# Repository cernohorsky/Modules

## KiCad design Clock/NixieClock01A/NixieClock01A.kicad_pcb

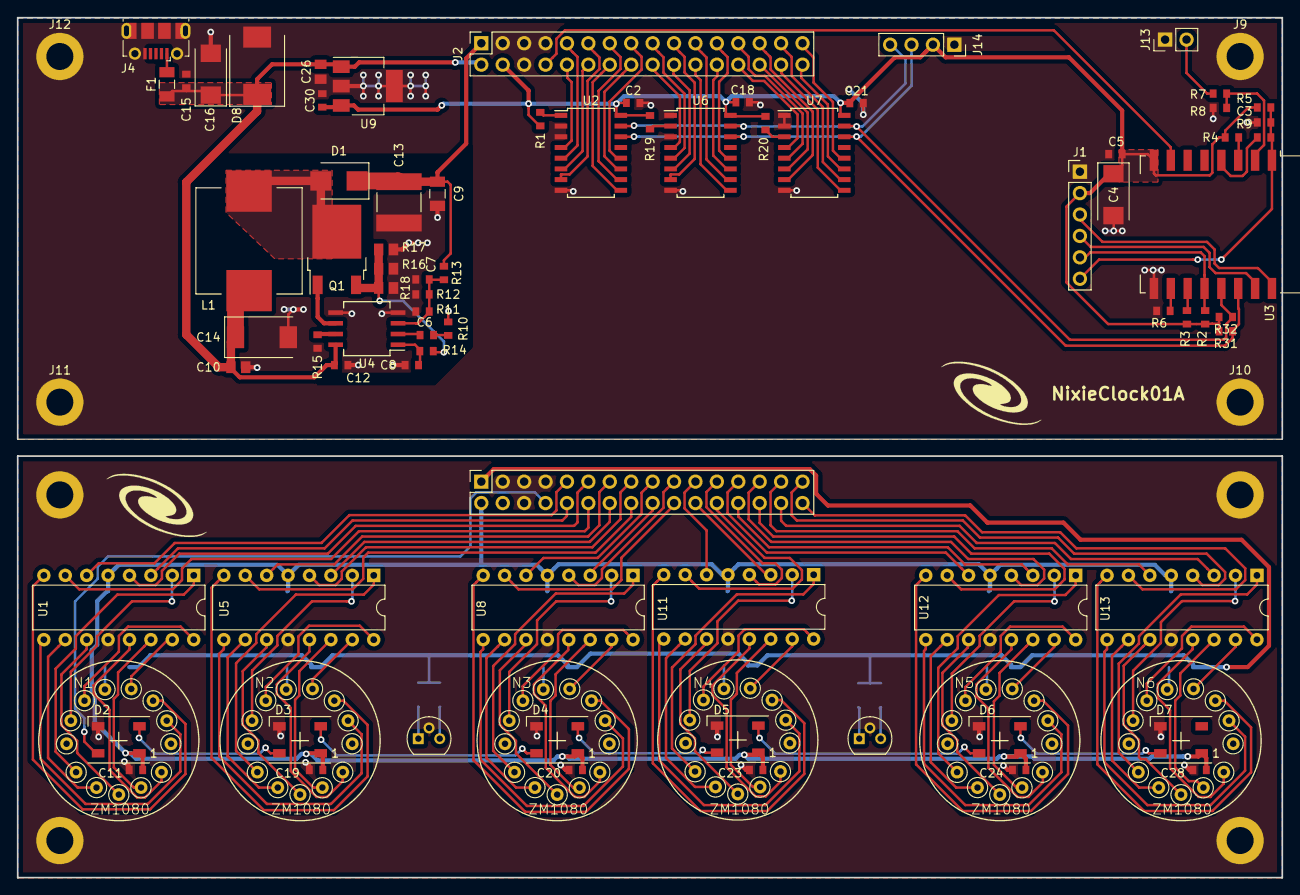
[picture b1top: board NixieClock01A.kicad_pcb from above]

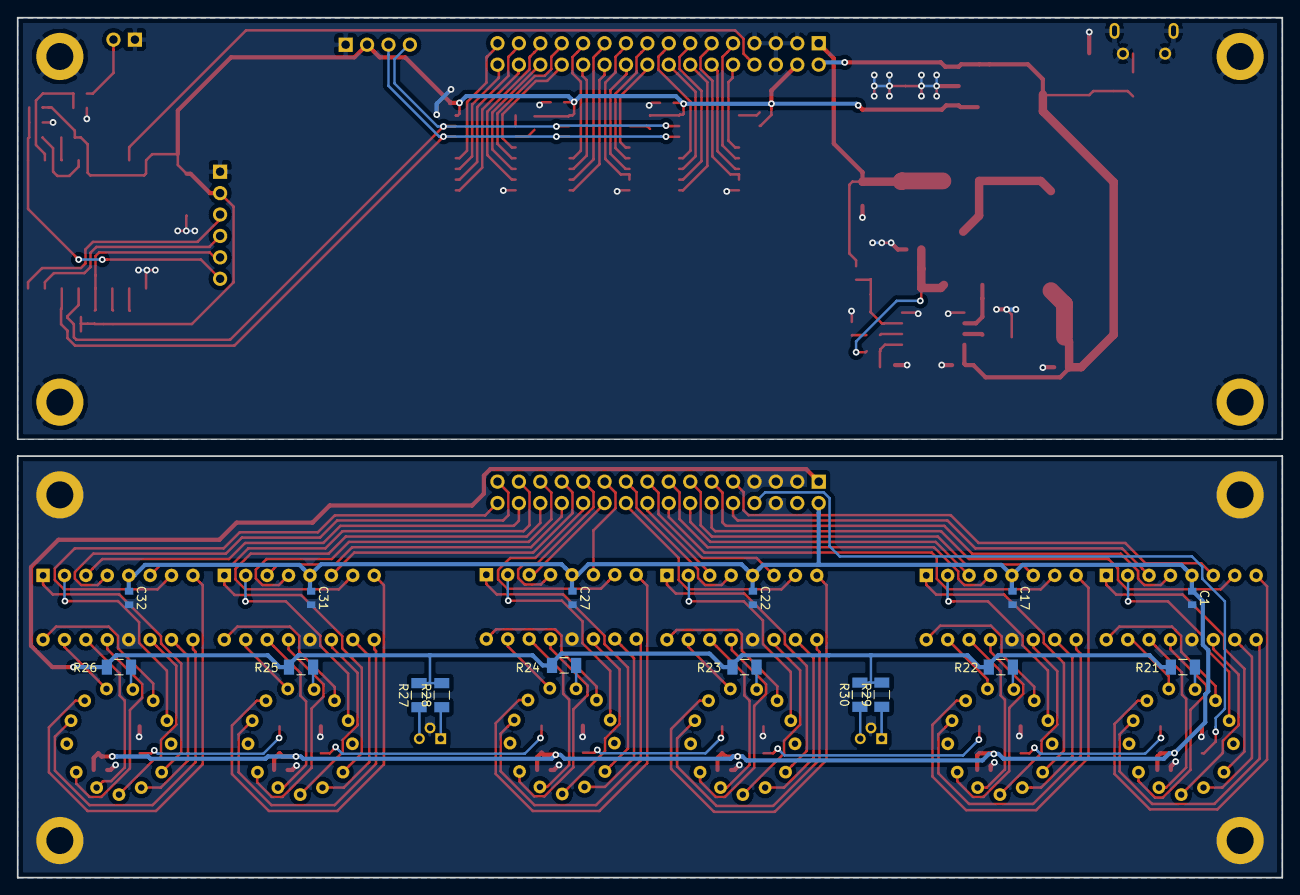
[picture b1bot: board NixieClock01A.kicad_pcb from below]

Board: 2 copper layers, 150.0 x 102.0 mm, 107 parts (16 on the bottom side), 128 nets.

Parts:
C1, C2, C3, C5, C11, C12, C15, C17, C18, C19, C20, C21, C22, C23, C24, C27, C28, C31, C32: 100n; C_0603_1608Metric
C4, C16: TPSC107K010R0075; CP_EIA-6032-28_Kemet-C
C6, C7: 22n; C_0603_1608Metric
C8: C; C_0603_1608Metric
C9: 100n/200V; C_1206_3216Metric
C10, C26: 10u; C_0805_2012Metric
C13: 1u/200V; C_2220_5650Metric
C14: 100u; CP_EIA-7343-31_Kemet-D
C30: 1u; C_0603_1608Metric
D1: D_Schottky; D_SMB
D2, D3, D4, D5, D6, D7: WS2812B; LED_WS2812B_PLCC4_5.0x5.0mm_P3.2mm
D8: D_TVS; D_SMC
F1: Fuse; Fuse_1206_3216Metric
J1: Conn_01x06_Male; PinHeader_1x06_P2.54mm_Vertical
J2, J3: Conn_02x16_Odd_Even; PinSocket_2x16_P2.54mm_Vertical
J4: USB_B_Micro; USB_Micro-B_Molex-105017-0001
J5, J6, J7, J8, J9, J10, J11, J12: Conn_01x01_Male; MountingHole_3.2mm_M3_DIN965_Pad
J13: Conn_01x02_Male; PinHeader_1x02_P2.54mm_Vertical
J14: Conn_01x04_Male; PinSocket_1x04_P2.54mm_Vertical
L1: L_Core_Ferrite; L_Wuerth_WE-PD-Typ-LS_Handsoldering
LA1, LA2: Lamp_Neon; TO-92
N1, N2, N3, N4, N5, N6: ZM1080
Q1: Q_NMOS_GDS; TO-252-2
R1, R11, R12, R13, R14, R19, R20: R; R_0603_1608Metric
R2, R3, R4, R5, R6: 12k; R_0603_1608Metric
R7: 330k; R_0603_1608Metric
R8: 100k; R_0603_1608Metric
R9: 470R; R_0603_1608Metric
R10: 4k7; R_0603_1608Metric
R15: 40k; R_0603_1608Metric
R16, R17, R18: R; R_0805_2012Metric
R21, R22, R23, R24, R25, R26: 27k; R_1206_3216Metric
R27, R28, R29, R30: 1M; R_1206_3216Metric
R31, R32: 4K7; R_0603_1608Metric
U1, U5, U8, U11, U12, U13: 74141; DIP-16_W7.62mm
U2, U6, U7: PCF8574; SOIC-16W_5.3x10.2mm_P1.27mm
U3: ESP-12E
U4: LM3478; SO-8_5.3x6.2mm_P1.27mm
U9: TC1262-33; SOT-223

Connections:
+3V3: C2.1, C4.1, C5.1, C18.1, C21.1, C30.1, J1.2, J2.4, J3.4, J14.2, R1.1, R2.2, R3.2, R4.2, R5.2, R19.1, R20.1, R31.2, R32.2, U2.16, U3.8, U6.16, U7.16, U9.3
+5V: C1.1, C10.1, C11.1, C12.1, C14.1, C15.1, C16.1, C17.1, C19.1, C20.1, C22.1, C23.1, C24.1, C26.1, C27.1, C28.1, C31.1, C32.1, D2.1, D3.1, D4.1, D5.1, D6.1, D7.1, D8.1, F1.1, J2.2, J3.2, L1.1, U1.5, U4.8, U5.5, U8.5, U9.1, U11.5, U12.5, U13.5
/A1: J2.10, J3.10, U1.3, U2.4
/A2: J2.9, J3.9, U1.6, U2.5
/A3: J2.12, J3.12, U1.7, U2.6
/A4: J2.11, J3.11, U1.4, U2.7
/ADC: R7.2, R8.1, U3.2
/ADC-IN: J13.2, R7.1
/B1: J2.14, J3.14, U2.9, U5.3
/B2: J2.13, J3.13, U2.10, U5.6
/B3: J2.16, J3.16, U2.11, U5.7
/B4: J2.15, J3.15, U2.12, U5.4
/C1: J2.18, J3.18, U6.4, U8.3
/C2: J2.17, J3.17, U6.5, U8.6
/C3: J2.20, J3.20, U6.6, U8.7
/C4: J2.19, J3.19, U6.7, U8.4
/D1: J2.22, J3.22, U6.9, U11.3
/D2: J2.21, J3.21, U6.10, U11.6
/D3: J2.24, J3.24, U6.11, U11.7
/D4: J2.23, J3.23, U6.12, U11.4
/E1: J2.26, J3.26, U7.4, U12.3
/E2: J2.25, J3.25, U7.5, U12.6
/E3: J2.28, J3.28, U7.6, U12.7
/E4: J2.27, J3.27, U7.7, U12.4
/EN: R4.1, U3.3
/F1: J2.30, J3.30, U7.9, U13.3
/F2: J2.29, J3.29, U7.10, U13.6
/F3: J2.32, J3.32, U7.11, U13.7
/F4: J2.31, J3.31, U7.12, U13.4
/GPIO0: J1.5, R2.1, U3.18
/GPIO2: R3.1, U3.17
/GPIO15: R6.1, U3.16
/NeoPix: D2.4, J2.8, J3.8, U3.7
/RST: C3.1, J1.6, R5.1, R9.1, U3.1
/RX: J1.4, U3.21
/SCL: J14.3, R31.1, U2.14, U3.20, U6.14, U7.14
/SDA: J14.4, R32.1, U2.15, U3.19, U6.15, U7.15
/TX: J1.3, U3.22
/Uanode: C9.1, C13.1, D1.1, J2.1, J3.1, R13.1, R21.1, R22.1, R23.1, R24.1, R25.1, R26.1, R27.2, R28.2, R29.2, R30.2
GND: C1.2, C2.2, C3.2, C4.2, C5.2, C7.1, C8.1, C9.2, C10.2, C11.2, C12.2, C13.2, C14.2, C15.2, C16.2, C17.2, C18.2, C19.2, C20.2, C21.2, C22.2, C23.2, C24.2, C26.2, C27.2, C28.2, C30.2, C31.2, C32.2, D2.3, D3.3, D4.3, D5.3, D6.3, D7.3, D8.2, J1.1, J2.3, J2.5, J2.6, J2.7, J3.3, J3.5, J3.6, J3.7, J4.5, J4.6, J5.1, J6.1, J7.1, J8.1, J9.1, J10.1, J11.1, J12.1, J13.1, J14.1, LA1.2, LA2.2, R6.2, R8.2, R10.1, R11.1, R12.1, R15.2, R16.2, R17.2, R18.2, U1.12, U2.2, U2.3, U2.8, U3.15, U4.4, U4.5, U5.12, U6.1, U6.3, U6.8, U7.1, U7.2, U7.8, U8.12, U9.2, U9.4, U11.12, U12.12, U13.12
unnamed: C6.1, U4.2
unnamed: C6.2, R10.2
unnamed: C7.2, R11.2, R12.2, R13.2, U4.3
unnamed: C8.2, R14.2, U4.1
unnamed: D1.2, L1.2, Q1.2
unnamed: D2.2, D3.4
unnamed: D3.2, D4.4
unnamed: D4.2, D5.4
unnamed: D5.2, D6.4
unnamed: D6.2, D7.4
unnamed: F1.2, J4.1
unnamed: LA1.1, R28.1
unnamed: LA1.3, R27.1
unnamed: LA2.1, R29.1
unnamed: LA2.3, R30.1
unnamed: N1.1, U1.15
unnamed: N1.2, U1.8
unnamed: N1.3, U1.9
unnamed: N1.5, U1.13
unnamed: N1.6, U1.14
unnamed: N1.7, U1.11
unnamed: N1.8, U1.10
unnamed: N1.9, U1.1
unnamed: N1.11, U1.2
unnamed: N1.12, U1.16
unnamed: N1.13, R21.2
unnamed: N2.1, U5.15
unnamed: N2.2, U5.8
unnamed: N2.3, U5.9
unnamed: N2.5, U5.13
unnamed: N2.6, U5.14
unnamed: N2.7, U5.11
unnamed: N2.8, U5.10
unnamed: N2.9, U5.1
unnamed: N2.11, U5.2
unnamed: N2.12, U5.16
unnamed: N2.13, R22.2
unnamed: N3.1, U8.15
unnamed: N3.2, U8.8
unnamed: N3.3, U8.9
unnamed: N3.5, U8.13
unnamed: N3.6, U8.14
unnamed: N3.7, U8.11
unnamed: N3.8, U8.10
unnamed: N3.9, U8.1
unnamed: N3.11, U8.2
unnamed: N3.12, U8.16
unnamed: N3.13, R23.2
unnamed: N4.1, U11.15
unnamed: N4.2, U11.8
unnamed: N4.3, U11.9
unnamed: N4.5, U11.13
unnamed: N4.6, U11.14
unnamed: N4.7, U11.11
unnamed: N4.8, U11.10
unnamed: N4.9, U11.1
unnamed: N4.11, U11.2
unnamed: N4.12, U11.16
unnamed: N4.13, R24.2
unnamed: N5.1, U12.15
unnamed: N5.2, U12.8
unnamed: N5.3, U12.9
unnamed: N5.5, U12.13
unnamed: N5.6, U12.14
unnamed: N5.7, U12.11
unnamed: N5.8, U12.10
unnamed: N5.9, U12.1
unnamed: N5.11, U12.2
unnamed: N5.12, U12.16
unnamed: N5.13, R25.2
unnamed: N6.1, U13.15
unnamed: N6.2, U13.8
unnamed: N6.3, U13.9
unnamed: N6.5, U13.13
unnamed: N6.6, U13.14
unnamed: N6.7, U13.11
unnamed: N6.8, U13.10
unnamed: N6.9, U13.1
unnamed: N6.11, U13.2
unnamed: N6.12, U13.16
unnamed: N6.13, R26.2
unnamed: Q1.1, U4.6
unnamed: Q1.3, R14.1, R16.1, R17.1, R18.1
unnamed: R1.2, U2.1
unnamed: R9.2, U3.4
unnamed: R15.1, U4.7
unnamed: R19.2, U6.2
unnamed: R20.2, U7.3

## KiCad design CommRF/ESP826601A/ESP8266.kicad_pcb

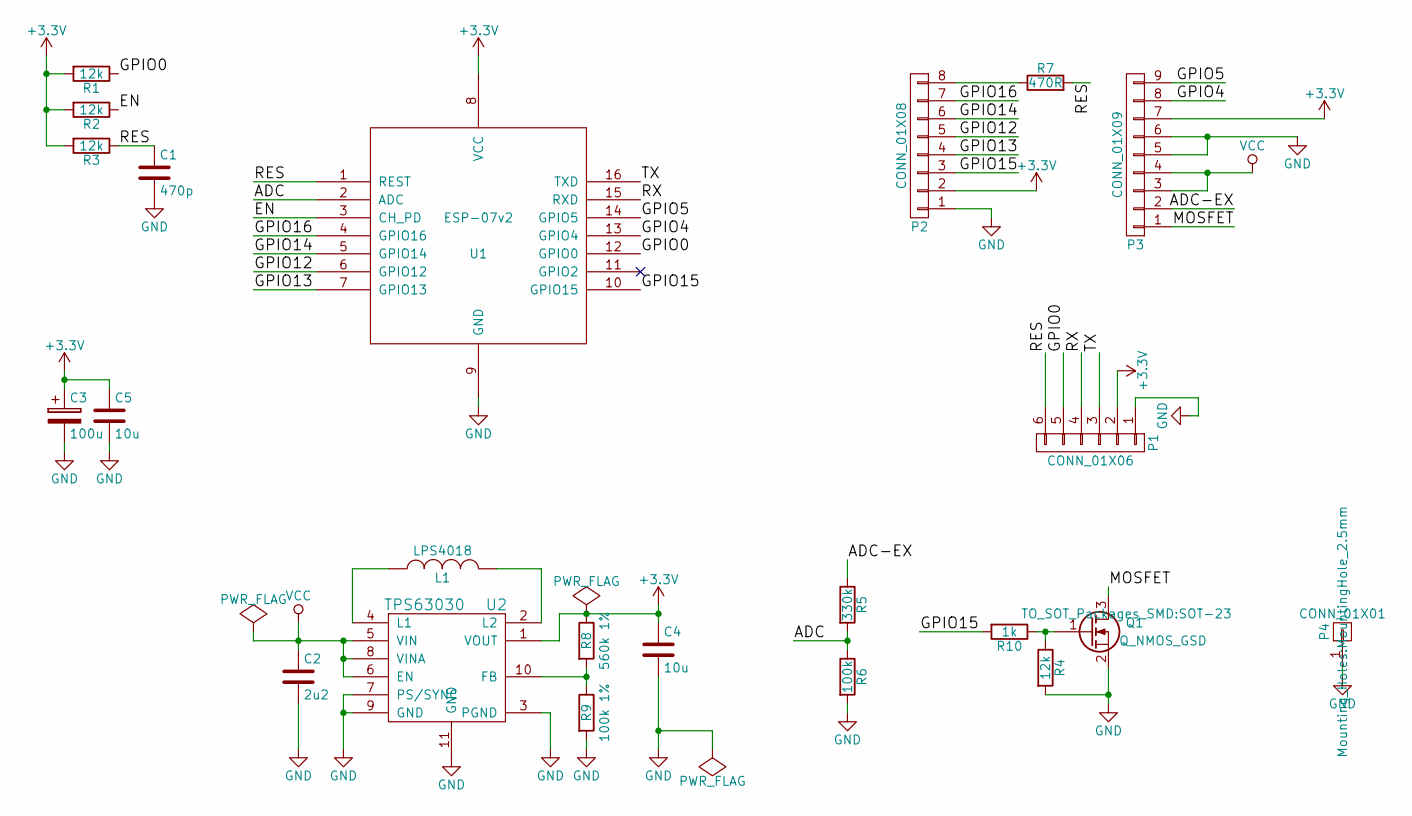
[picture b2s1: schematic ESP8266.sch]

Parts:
C1: 470p; C_0603
C2: 2u2; C_0603
C3: 100u; TantalC_SizeB_EIA-3528_Wave
C4, C5: 10u; C_0805
L1: LPS4018
P1: CONN_01X06; Pin_Header_Straight_1x06
P2: CONN_01X08; Pin_Header_Straight_1x08
P3: CONN_01X09; Pin_Header_Straight_1x09
P4: CONN_01X01; MountingHole_2.5mm
Q1: Q_NMOS_GSD; SOT-23
R1, R2, R3, R4: 12k; R_0603
R5: 330k; R_0603
R6: 100k; R_0603
R7: 470R; R_0603
R8: 560k 1%; R_0603
R9: 100k 1%; R_0603
R10: 1k; R_0603
U1: ESP-07v2
U2: TPS63030; DSK-10Pin-VSON

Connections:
+3V3: C3.1, C4.1, C5.1, P1.2, P2.2, P3.7, R1.2, R2.2, R3.2, R8.1, U1.8 (VCC), U2.1 (VOUT)
/ADC: R5.2, R6.1, U1.2 (ADC)
/ADC-EX: P3.2, R5.1
/EN: R2.1, U1.3 (CH_PD)
/GPIO0: P1.5, R1.1, U1.12 (GPIO0)
/GPIO4: P3.8, U1.13 (GPIO4)
/GPIO5: P3.9, U1.14 (GPIO5)
/GPIO12: P2.5, U1.6 (GPIO12)
/GPIO13: P2.4, U1.7 (GPIO13)
/GPIO14: P2.6, U1.5 (GPIO14)
/GPIO15: P2.3, R10.2, U1.10 (GPIO15)
/GPIO16: P2.7, U1.4 (GPIO16)
/MOSFET: P3.1, Q1.3 (D)
/RES: C1.1, P1.6, R3.1, R7.2, U1.1 (REST)
/RX: P1.4, U1.15 (RXD)
/TX: P1.3, U1.16 (TXD)
GND: C1.2, C2.2, C3.2, C4.2, C5.2, P1.1, P2.1, P3.5, P3.6, P4.1, Q1.2 (S), R4.2, R6.2, R9.2, U1.9 (GND), U2.3 (PGND), U2.7 (PS/SYNC), U2.9 (GND), U2.11 (GND)
unnamed: L1.1, U2.4 (L1)
unnamed: L1.2, U2.2 (L2)
unnamed: P2.8, R7.1
unnamed: Q1.1 (G), R4.1, R10.1
unnamed: R8.2, R9.1, U2.10 (FB)
VCC: C2.1, P3.3, P3.4, U2.5 (VIN), U2.6 (EN), U2.8 (VINA)

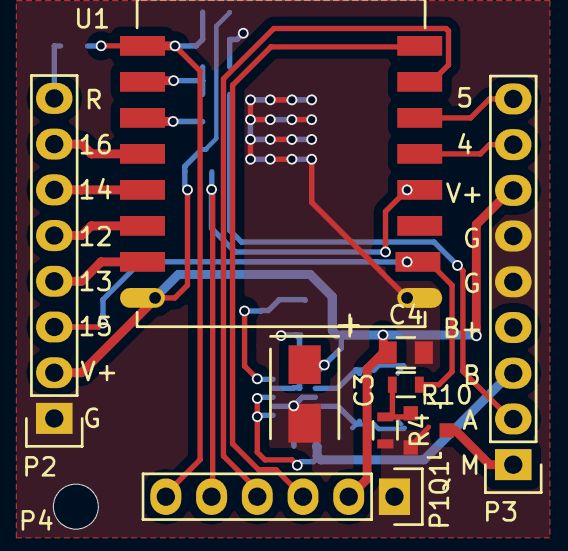
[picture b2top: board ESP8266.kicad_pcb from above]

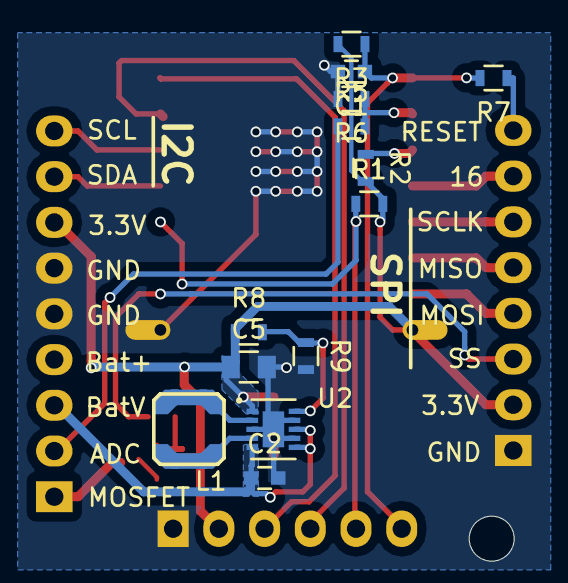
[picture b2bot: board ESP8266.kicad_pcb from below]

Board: 2 copper layers, 23 parts (13 on the bottom side), 23 nets.

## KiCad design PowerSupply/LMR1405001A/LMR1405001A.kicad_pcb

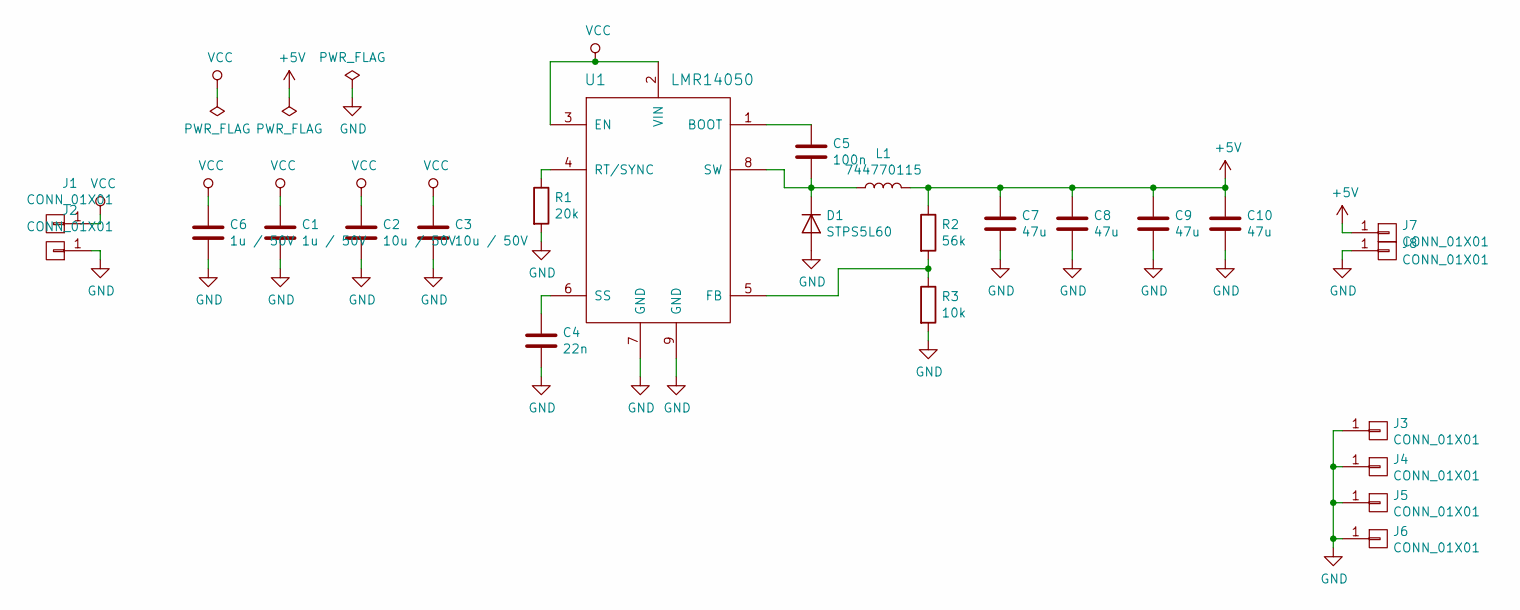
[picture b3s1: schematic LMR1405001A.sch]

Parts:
C1, C6: 1u / 50V; C_1210
C2, C3: 10u / 50V; C_1210
C4: 22n; C_0603
C5: 100n; C_0603
C7, C8, C9, C10: 47u; C_1210
D1: STPS5L60; DO-214AB
J1, J2, J7, J8: CONN_01X01; WAGO256_2
J3, J4, J5, J6: CONN_01X01; MountingHole_3.2mm_M3_Pad
L1: 744770115; SELF-WE-PD-XXL
R1: 20k; C_0603
R2: 56k; C_0603
R3: 10k; C_0603
U1: LMR14050; HSOP-8

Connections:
+5V: C7.1, C8.1, C9.1, C10.1, J7.1, L1.2, R2.1
GND: C1.2, C2.2, C3.2, C4.2, C6.2, C7.2, C8.2, C9.2, C10.2, D1.2 (A), J2.1, J3.1, J4.1, J5.1, J6.1, J8.1, R1.2, R3.2, U1.7 (GND), U1.9 (GND)
unnamed: C4.1, U1.6 (SS)
unnamed: C5.1, U1.1 (BOOT)
unnamed: C5.2, D1.1 (K), L1.1, U1.8 (SW)
unnamed: R1.1, U1.4 (RT/SYNC)
unnamed: R2.2, R3.1, U1.5 (FB)
VCC: C1.1, C2.1, C3.1, C6.1, J1.1, U1.2 (VIN), U1.3 (EN)

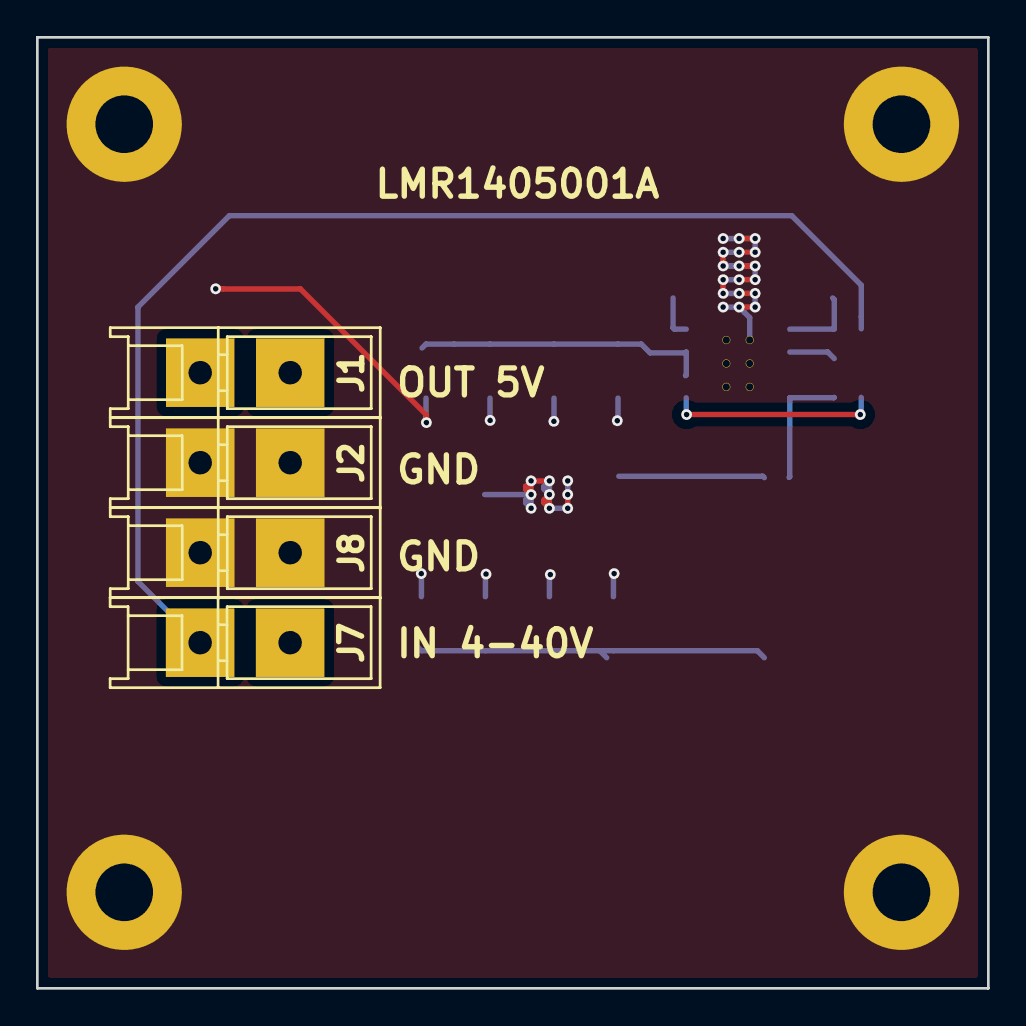
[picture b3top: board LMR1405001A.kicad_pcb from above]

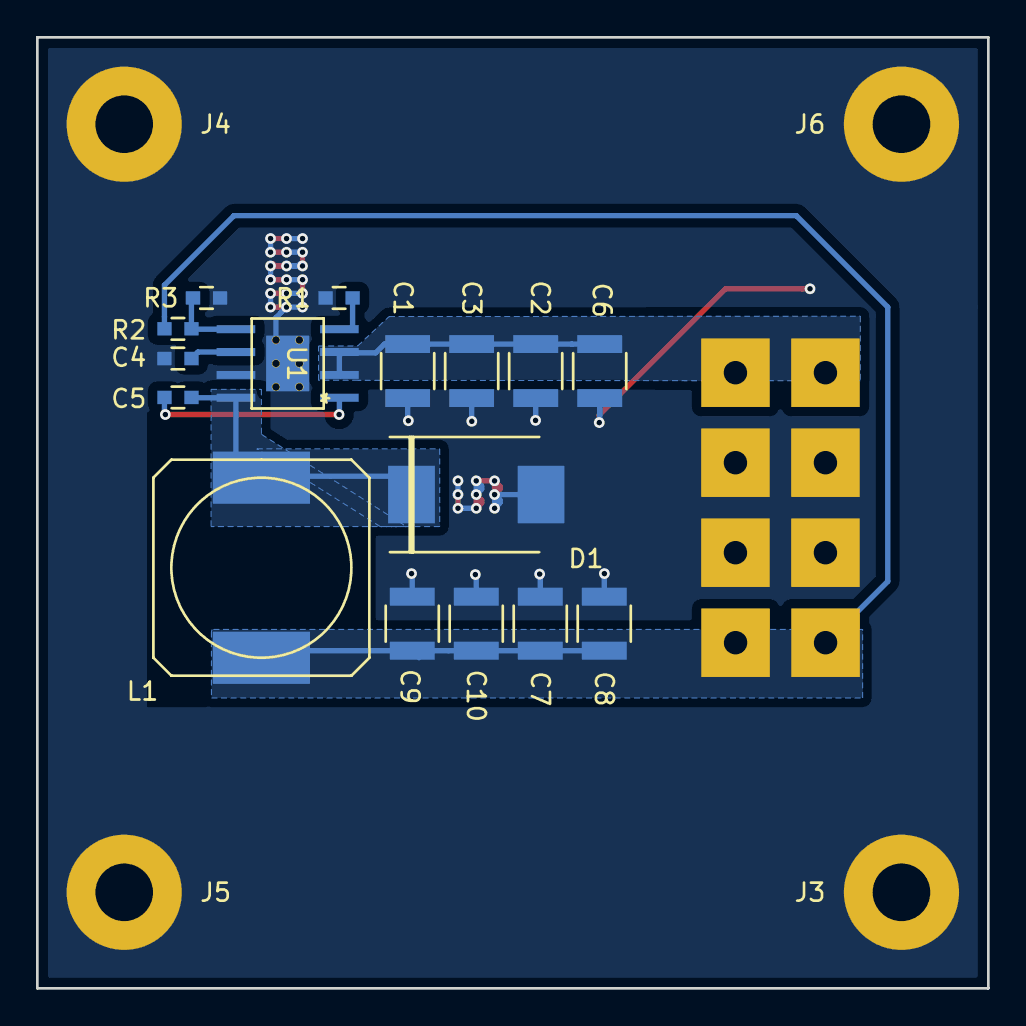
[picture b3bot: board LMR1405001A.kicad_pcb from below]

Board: 2 copper layers, 52.8 x 52.8 mm, 24 parts (20 on the bottom side), 8 nets.

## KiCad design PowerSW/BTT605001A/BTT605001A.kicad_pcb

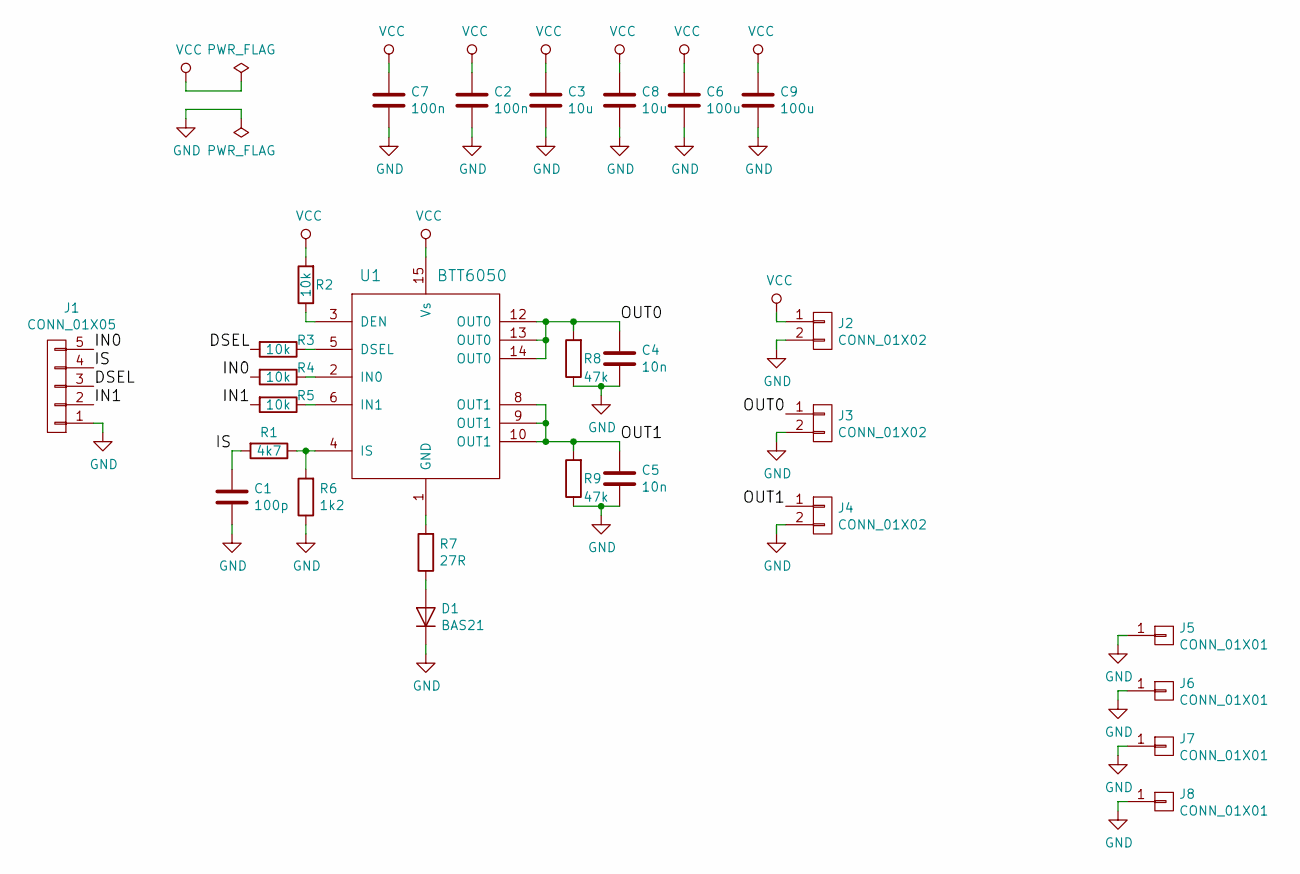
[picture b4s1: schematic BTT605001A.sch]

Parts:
C1: 100p; C_0603
C2, C7: 100n; C_0603
C3, C8: 10u; C_1210
C4, C5: 10n; C_0603
C6, C9: 100u; c_elec_10x10.5
D1: BAS21; C_0603
J1: CONN_01X05; Pin_Header_Straight_1x05
J2, J3, J4: CONN_01X02; WireConnection_2.50mmDrill
J5, J6, J7, J8: CONN_01X01; MountingHole_3.2mm_M3_DIN965_Pad
R1: 4k7; R_0603
R2, R3, R4, R5: 10k; R_0603
R6: 1k2; R_0603
R7: 27R; R_0603
R8, R9: 47k; R_0603
U1: BTT6050; PG-DSO-14-47_3.9x8.7mm_Pitch1.27mm

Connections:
/DSEL: J1.3, R3.2
/IN0: J1.5, R4.2
/IN1: J1.2, R5.2
/IS: C1.1, J1.4, R1.2
/OUT0: C4.1, J3.1, R8.2, U1.12 (OUT0), U1.13 (OUT0), U1.14 (OUT0)
/OUT1: C5.1, J4.1, R9.2, U1.8 (OUT1), U1.9 (OUT1), U1.10 (OUT1)
GND: C1.2, C2.2, C3.2, C4.2, C5.2, C6.2, C7.2, C8.2, C9.2, D1.1 (K), J1.1, J2.2, J3.2, J4.2, J5.1, J6.1, J7.1, J8.1, R6.1, R8.1, R9.1
unnamed: D1.2 (A), R7.1
unnamed: R1.1, R6.2, U1.4 (IS)
unnamed: R2.1, U1.3 (DEN)
unnamed: R3.1, U1.5 (DSEL)
unnamed: R4.1, U1.2 (IN0)
unnamed: R5.1, U1.6 (IN1)
unnamed: R7.2, U1.1 (GND)
VCC: C2.1, C3.1, C6.1, C7.1, C8.1, C9.1, J2.1, R2.2, U1.15 (Vs)

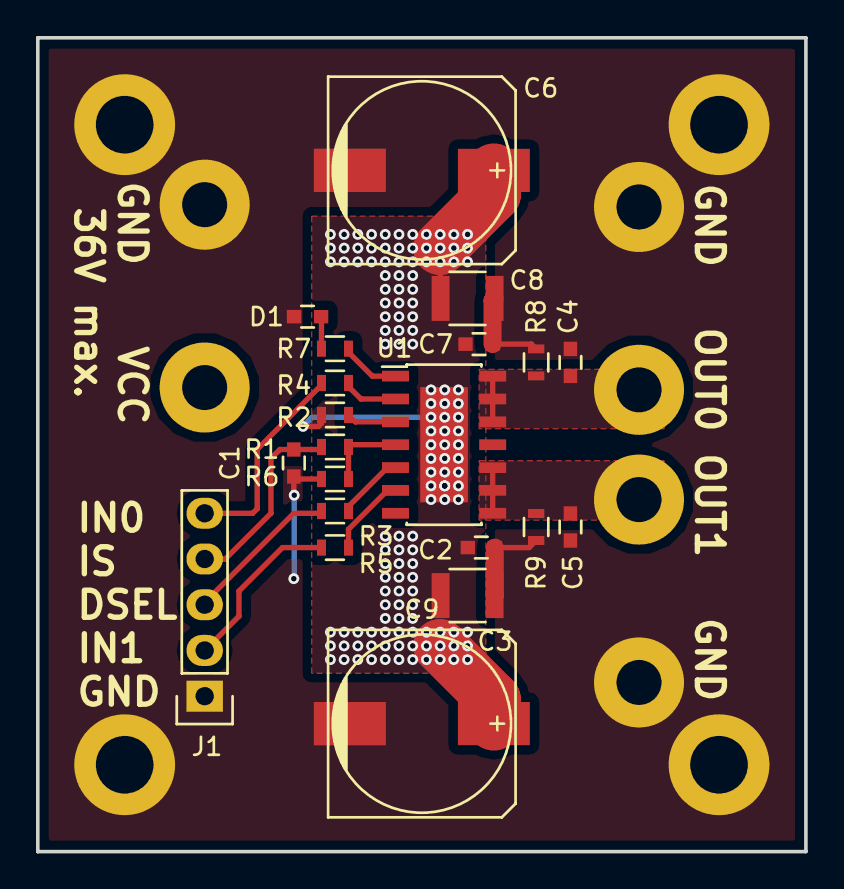
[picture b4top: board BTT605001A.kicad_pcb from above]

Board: 2 copper layers, 42.7 x 45.2 mm, 28 parts (0 on the bottom side), 15 nets.

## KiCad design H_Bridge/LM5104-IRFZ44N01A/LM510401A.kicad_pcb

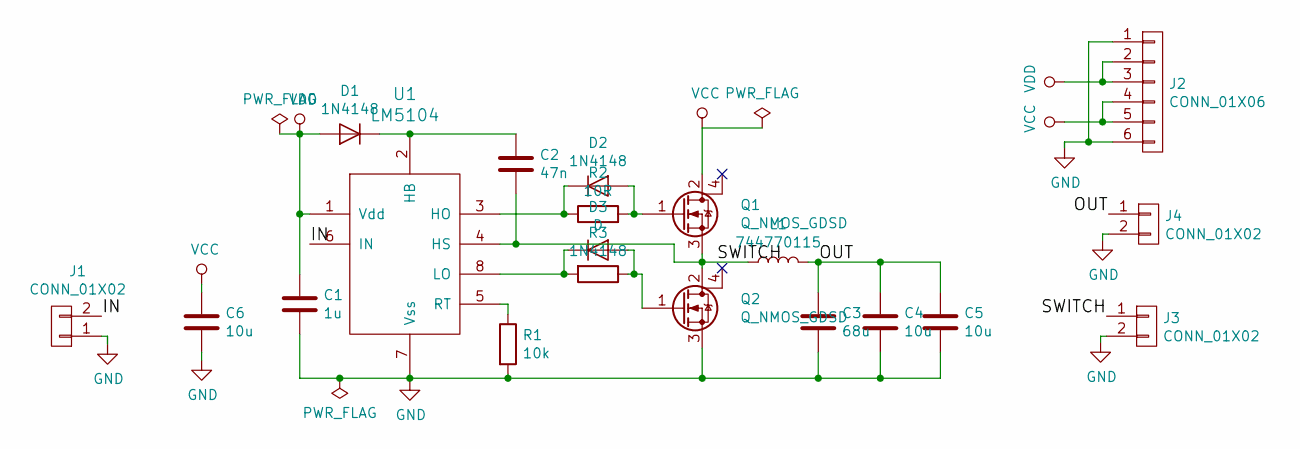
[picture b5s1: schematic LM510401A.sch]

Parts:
C1: 1u; C_0805
C2: 47n; C_0603
C3: 68u; C_1210
C4, C5, C6: 10u; C_1210
D1, D2: 1N4148; C_0603
D3: D; C_0603
J1, J3, J4: CONN_01X02; Pin_Header_Straight_1x02
J2: CONN_01X06; Pin_Header_Straight_1x06
L1: 744770115; SELF-WE-PD-XXL
Q1, Q2: Q_NMOS_GDSD; TO-220_Neutral123_Vertical
R1: 10k; R_0603
R2: 10R; R_0603
R3: 1N4148; R_0603
U1: LM5104; SOIC-8-N

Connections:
/IN: J1.2, U1.6 (IN)
/OUT: C3.1, C4.1, C5.1, J4.1, L1.2
/SWITCH: C2.2, J3.1, L1.1, Q1.3 (S), Q2.2 (D), U1.4 (HS)
GND: C1.2, C3.2, C4.2, C5.2, C6.2, J1.1, J2.1, J2.6, J3.2, J4.2, Q2.3 (S), R1.2, U1.7 (Vss)
unnamed: C2.1, D1.1 (K), U1.2 (HB)
unnamed: D2.1 (K), R2.1, U1.3 (HO)
unnamed: D2.2 (A), Q1.1 (G), R2.2
unnamed: D3.1 (K), R3.2, U1.8 (LO)
unnamed: D3.2 (A), Q2.1 (G), R3.1
unnamed: R1.1, U1.5 (RT)
VCC: C6.1, J2.4, J2.5, Q1.2 (D)
VDD: C1.1, D1.2 (A), J2.2, J2.3, U1.1 (Vdd)

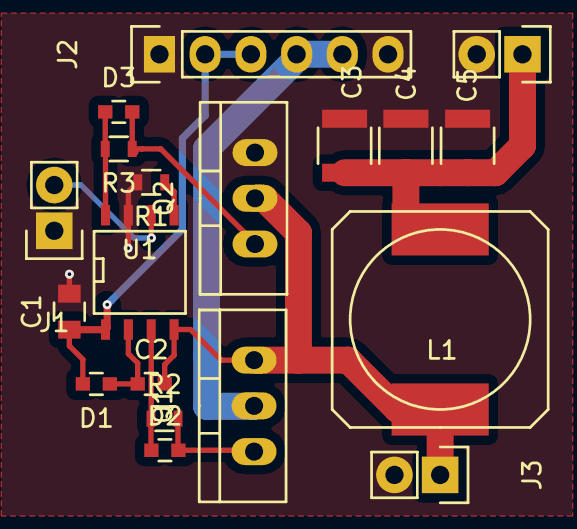
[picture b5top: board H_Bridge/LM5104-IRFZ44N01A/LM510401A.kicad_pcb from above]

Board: 2 copper layers, 20 parts (1 on the bottom side), 12 nets.

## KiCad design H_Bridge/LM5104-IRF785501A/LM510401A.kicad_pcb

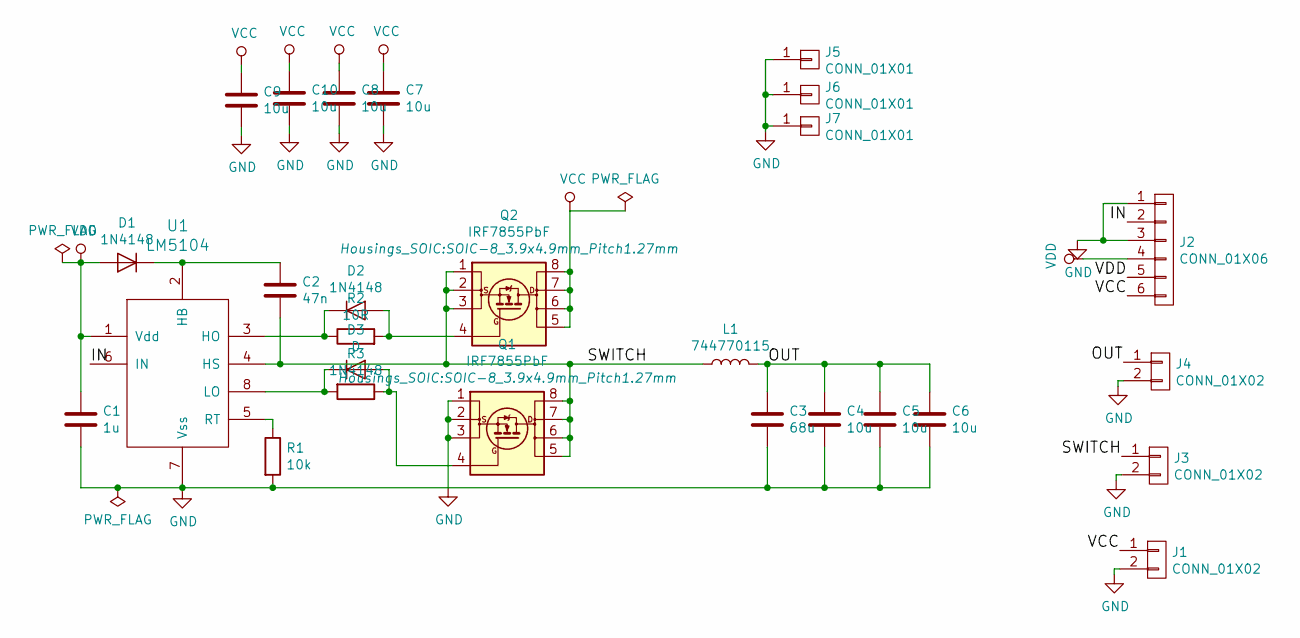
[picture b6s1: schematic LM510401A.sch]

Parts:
C1: 1u; C_0805
C2: 47n; C_0603
C3: 68u; C_1210
C4, C5, C6, C7, C8, C9, C10: 10u; C_1210
D1, D2: 1N4148; C_0603
D3: D; C_0603
J1, J4: CONN_01X02; WireConnection_2.00mmDrill
J2: CONN_01X06; Pin_Header_Straight_1x06
J3: CONN_01X02; Pin_Header_Straight_1x02
J5, J6, J7: CONN_01X01; MountingHole_3.2mm_M3_Pad
L1: 744770115; SELF-WE-PD-XXL
Q1, Q2: IRF7855PbF; SOIC-8_3.9x4.9mm_Pitch1.27mm
R1: 10k; R_0603
R2: 10R; R_0603
R3: 1N4148; R_0603
U1: LM5104; SOIC-8-N

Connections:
/IN: J2.2, U1.6 (IN)
/OUT: C3.1, C4.1, C5.1, C6.1, J4.1, L1.2
/SWITCH: C2.2, J3.1, L1.1, Q1.5 (D), Q1.6 (D), Q1.7 (D), Q1.8 (D), Q2.1 (S), Q2.2 (S), Q2.3 (S), U1.4 (HS)
GND: C1.2, C3.2, C4.2, C5.2, C6.2, C7.2, C8.2, C9.2, C10.2, J1.2, J2.1, J2.3, J3.2, J4.2, J5.1, J6.1, J7.1, Q1.1 (S), Q1.2 (S), Q1.3 (S), R1.2, U1.7 (Vss)
unnamed: C2.1, D1.1 (K), U1.2 (HB)
unnamed: D2.1 (K), R2.1, U1.3 (HO)
unnamed: D2.2 (A), Q2.4 (G), R2.2
unnamed: D3.1 (K), R3.2, U1.8 (LO)
unnamed: D3.2 (A), Q1.4 (G), R3.1
unnamed: R1.1, U1.5 (RT)
VCC: C7.1, C8.1, C9.1, C10.1, J1.1, J2.6, Q2.5 (D), Q2.6 (D), Q2.7 (D), Q2.8 (D)
VDD: C1.1, D1.2 (A), J2.4, J2.5, U1.1 (Vdd)

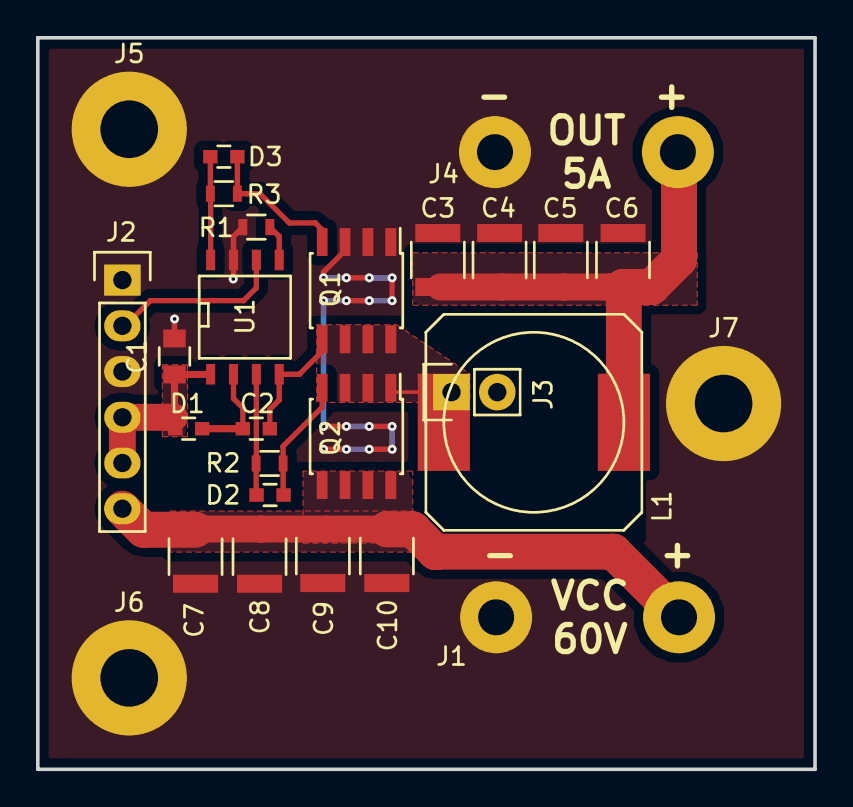
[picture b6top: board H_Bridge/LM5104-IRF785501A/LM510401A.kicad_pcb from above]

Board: 2 copper layers, 43.2 x 40.6 mm, 27 parts (0 on the bottom side), 12 nets.

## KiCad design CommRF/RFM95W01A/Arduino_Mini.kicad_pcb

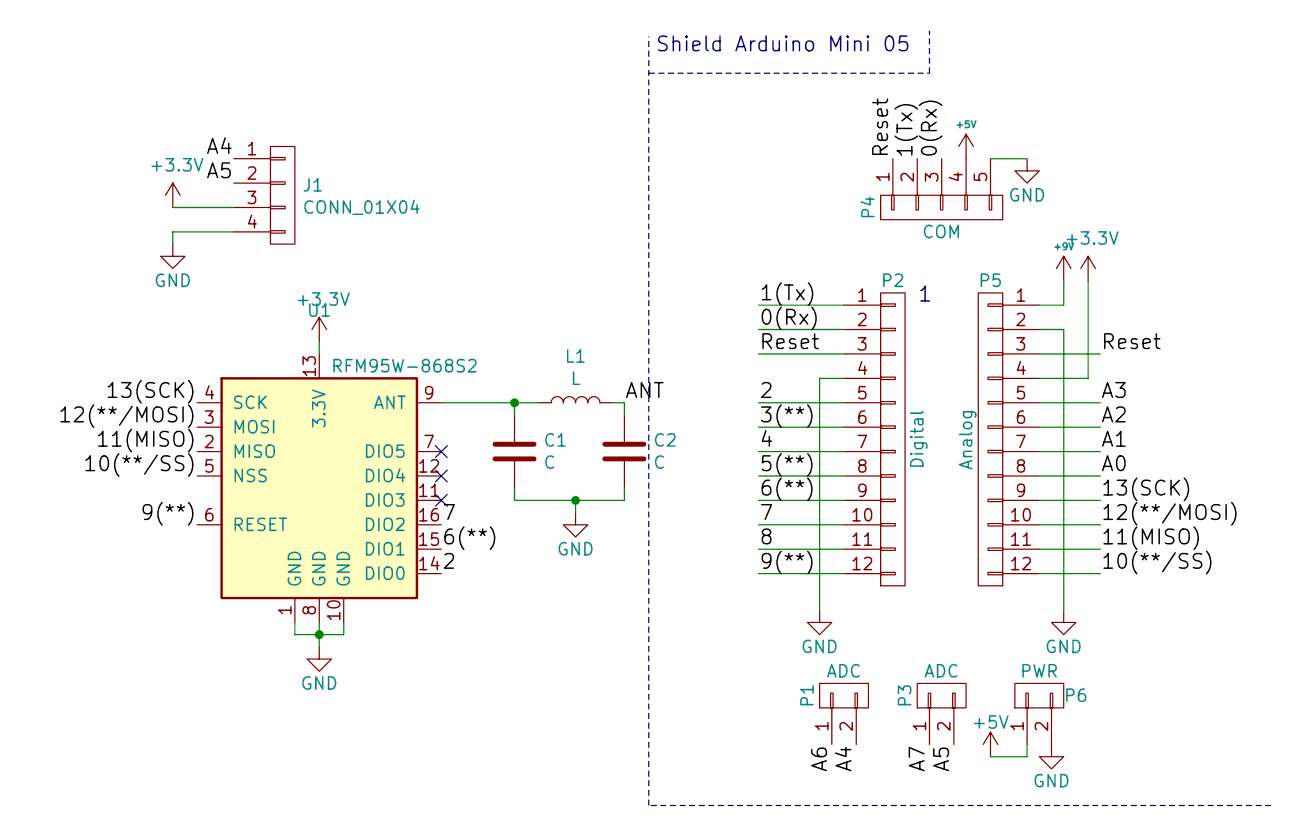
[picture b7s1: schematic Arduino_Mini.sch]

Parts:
C1, C2: C; C_0402
J1: CONN_01X04; RJ12GLP-AMP(RJ12)
L1: L; C_0402
P1, P3: ADC; Socket_Strip_Arduino_1x02
P2: Digital; Socket_Strip_Arduino_1x12
P4: COM; Socket_Strip_Arduino_1x05
P5: Analog; Socket_Strip_Arduino_1x12
P6: PWR; Socket_Strip_Arduino_1x02
U1: RFM95W-868S2; RFM95W

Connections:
+3V3: J1.3, P5.4, U1.13 (3.3V)
+5V: P4.4, P6.1
+9V: P5.1
/0(Rx): P2.2, P4.3
/1(Tx): P2.1, P4.2
/2: P2.5, U1.14 (DIO0)
/3(**): P2.6
/4: P2.7
/5(**): P2.8
/6(**): P2.9, U1.15 (DIO1)
/7: P2.10, U1.16 (DIO2)
/8: P2.11
/9(**): P2.12, U1.6 (RESET)
/10(**/SS): P5.12, U1.5 (NSS)
/11(MISO): P5.11, U1.2 (MISO)
/12(**/MOSI): P5.10, U1.3 (MOSI)
/13(SCK): P5.9, U1.4 (SCK)
/A0: P5.8
/A1: P5.7
/A2: P5.6
/A3: P5.5
/A4: J1.1, P1.2
/A5: J1.2, P3.2
/A6: P1.1
/A7: P3.1
/ANT: C2.1, L1.2
/Reset: P2.3, P4.1, P5.3
GND: C1.2, C2.2, J1.4, P2.4, P4.5, P5.2, P6.2, U1.1 (GND), U1.8 (GND), U1.10 (GND)
unnamed: C1.1, L1.1, U1.9 (ANT)

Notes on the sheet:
Shield Arduino Mini 05

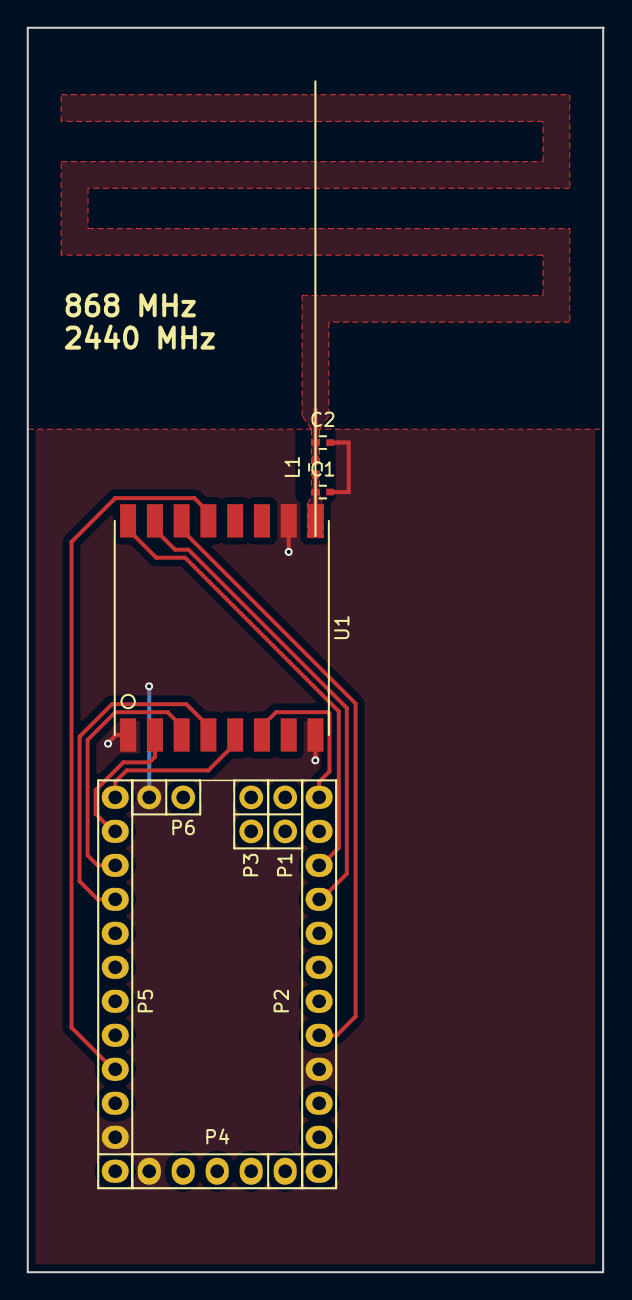
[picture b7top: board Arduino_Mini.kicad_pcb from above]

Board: 2 copper layers, 43.0 x 93.0 mm, 10 parts (0 on the bottom side), 16 nets.
